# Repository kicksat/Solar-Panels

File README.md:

# solar-panels

Solar panels for the KickSat-2 CubeSat

# License

[Creative Commons Attribution-ShareAlike 4.0 International](https://creativecommons.org/licenses/by-sa/4.0/)

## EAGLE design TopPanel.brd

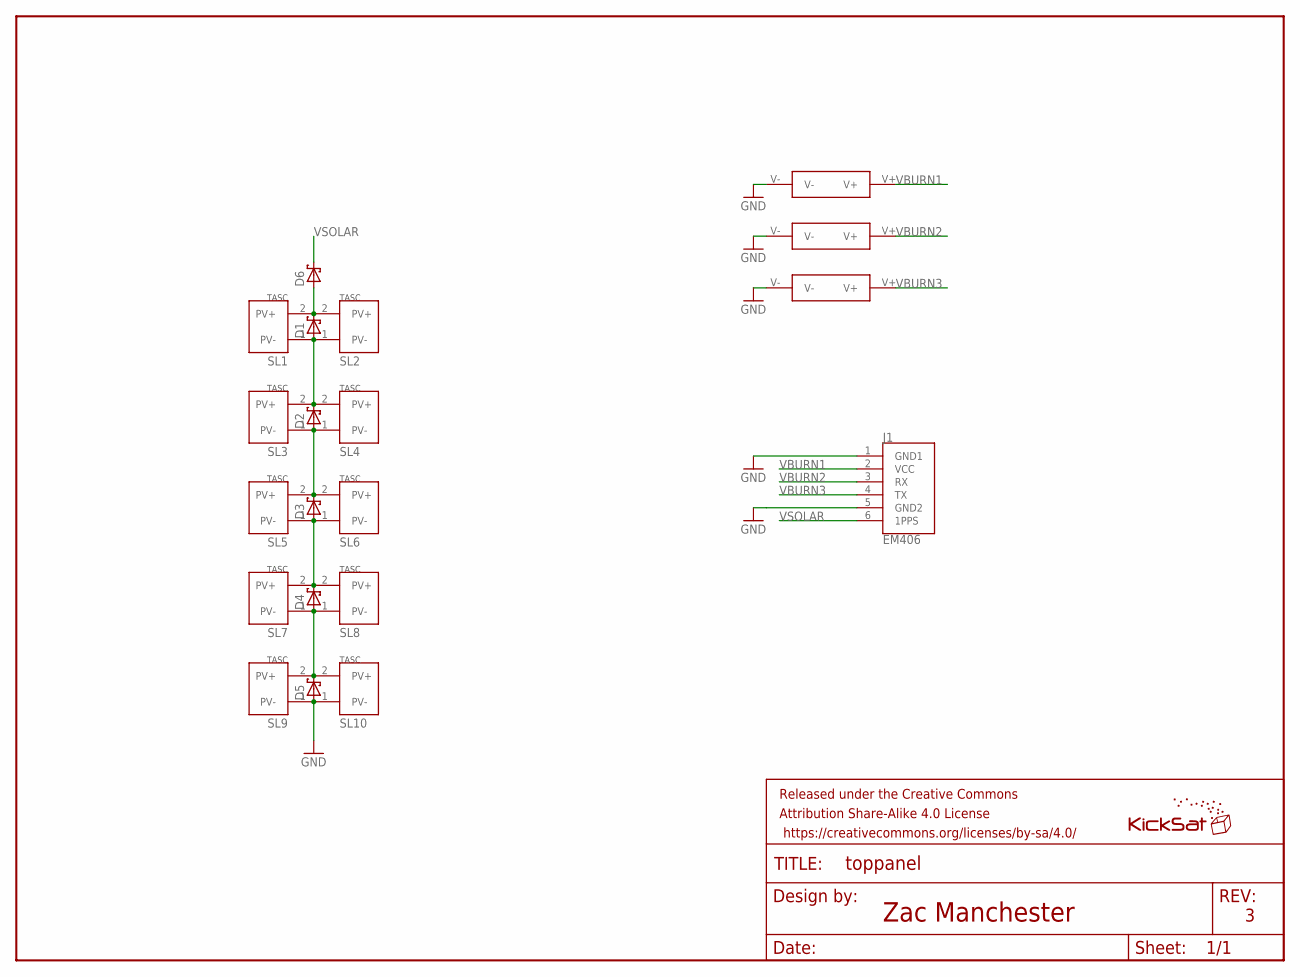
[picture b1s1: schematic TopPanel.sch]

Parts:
D1, D2, D3, D4, D5, D6: SB_DIODE
FRAME1: FRAME-LETTER; CREATIVE_COMMONS
J1: EM406; 1X06-1MM
SL1, SL2, SL3, SL4, SL5, SL6, SL7, SL8, SL9, SL10: SOLAR_CELL
U$1: KICKSAT_LOGO
U$2, U$3, U$4: BURNWIRE

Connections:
GND: D5.POS, J1.1 (GND1), J1.5 (GND2), SL9.1 (PV-), SL10.1 (PV-), U$2.V-, U$3.V-, U$4.V-
unnamed: D1.NEG, D6.POS, SL1.2 (PV+), SL2.2 (PV+)
unnamed: D2.POS, D3.NEG, SL3.1 (PV-), SL4.1 (PV-), SL5.2 (PV+), SL6.2 (PV+)
unnamed: D3.POS, D4.NEG, SL5.1 (PV-), SL6.1 (PV-), SL7.2 (PV+), SL8.2 (PV+)
unnamed: D1.POS, D2.NEG, SL1.1 (PV-), SL2.1 (PV-), SL3.2 (PV+), SL4.2 (PV+)
unnamed: D4.POS, D5.NEG, SL7.1 (PV-), SL8.1 (PV-), SL9.2 (PV+), SL10.2 (PV+)
VBURN1: J1.2 (VCC), U$2.V+
VBURN2: J1.3 (RX), U$3.V+
VBURN3: J1.4 (TX), U$4.V+
VSOLAR: D6.NEG, J1.6 (1PPS)

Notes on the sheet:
Zac Manchester

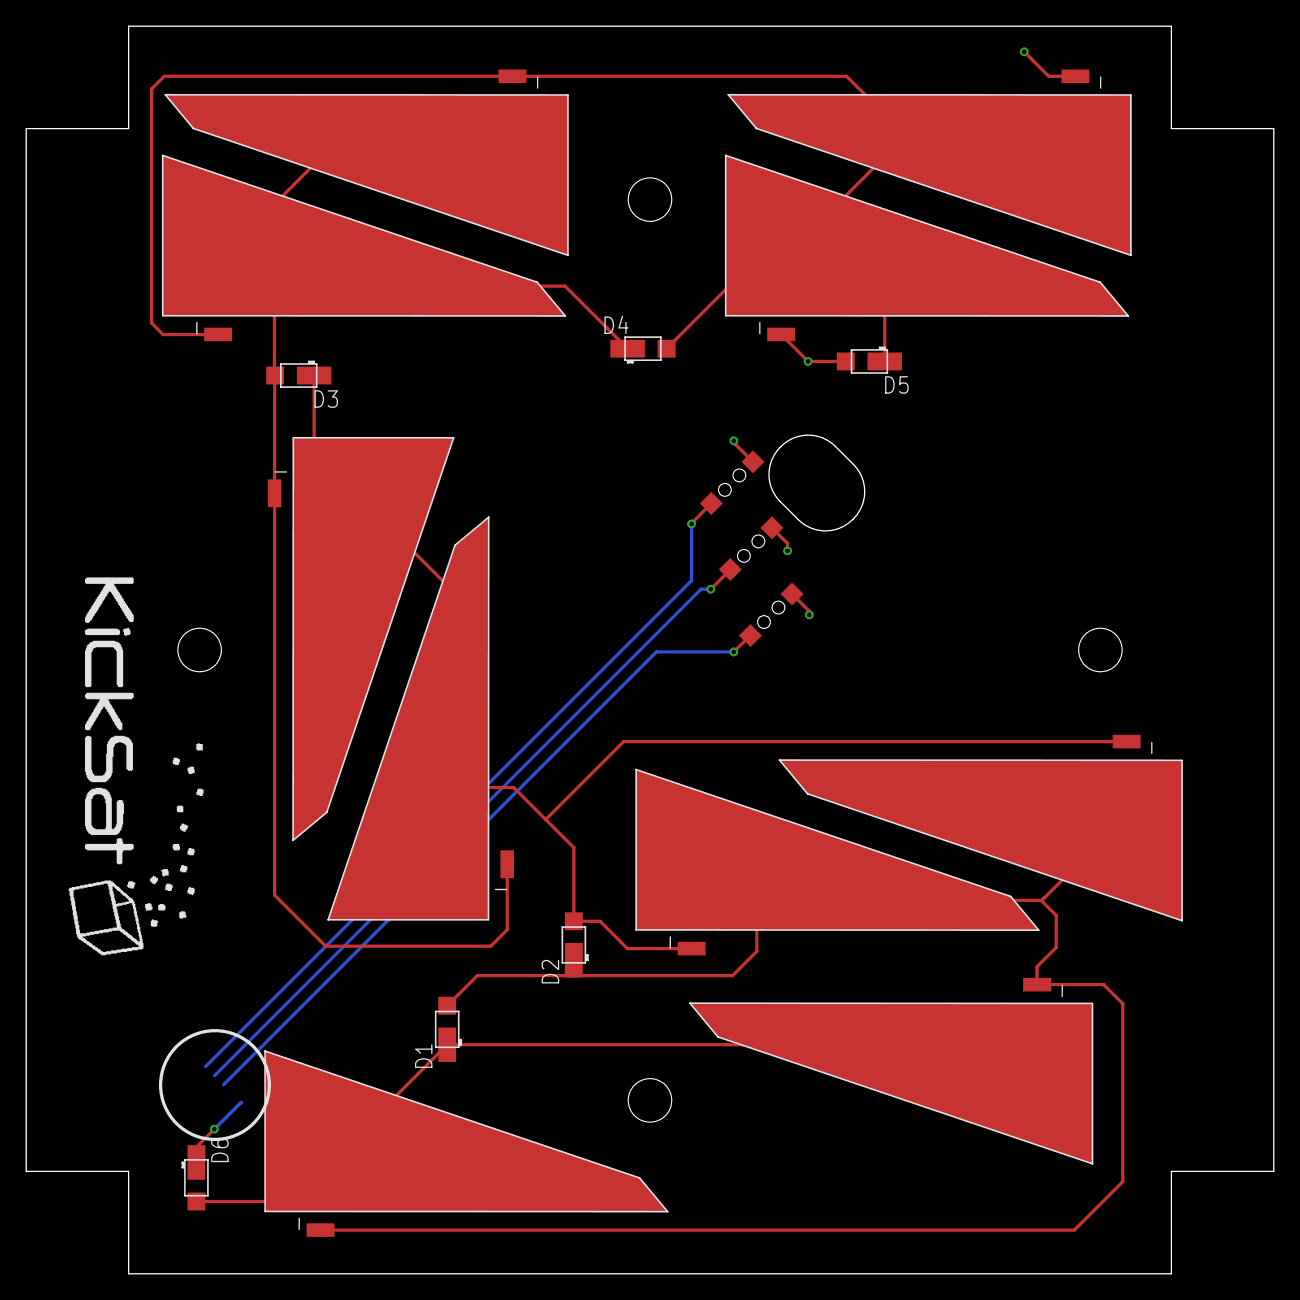
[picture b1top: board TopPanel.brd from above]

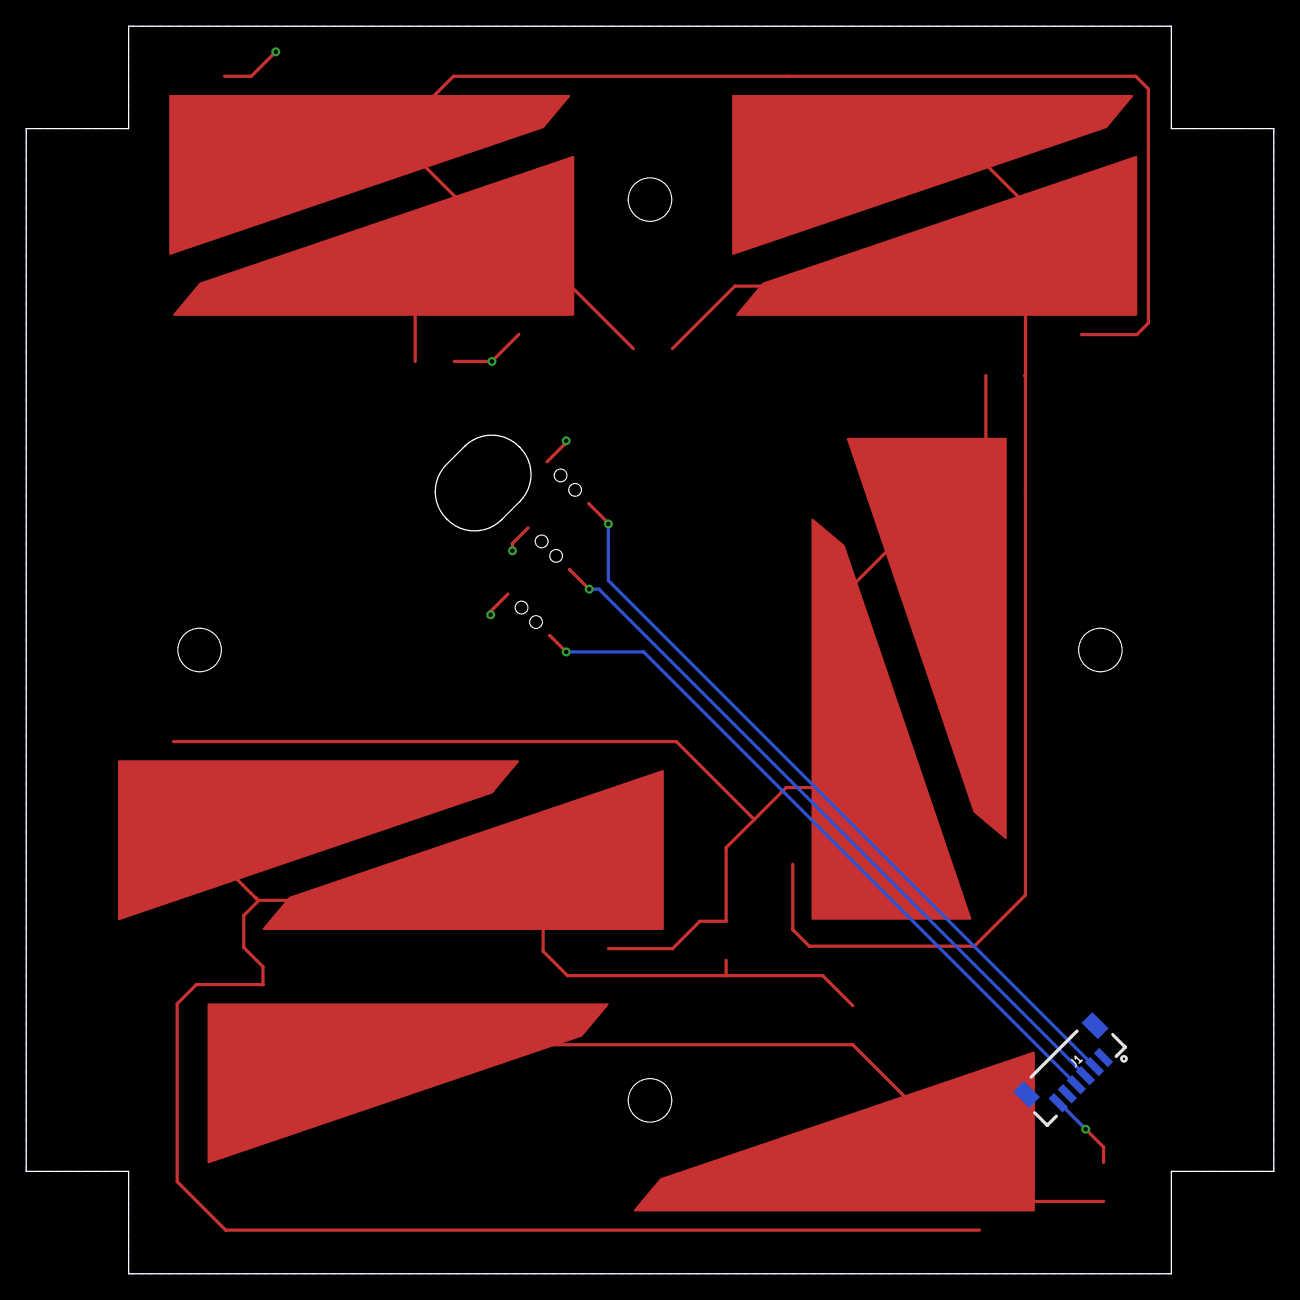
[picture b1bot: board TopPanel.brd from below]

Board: 2 copper layers, 97.5 x 97.5 mm, 22 parts (2 on the bottom side), 10 nets.

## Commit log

2018-04-11 Initial commit of KickSat-2 solar panels
2018-07-20 Set theme jekyll-theme-midnight
2018-08-27 New top panel outline
2018-08-27 Holes in the right spots...
2018-08-27 Connector swap
2018-08-28 put connector in correct spot
2018-08-28 Started routing
2018-08-29 Finished layout
2018-08-29 Adding Gerbers

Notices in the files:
parts and their libraries:
SparkFun-Aesthetics: Licensing: Creative Commons ShareAlike 4.0 International - https://creativecommons.org/licenses/by-sa/4.0
SparkFun-Aesthetics: Released under the Creative Commons Attribution Share-Alike 4.0 License
SparkFun-Aesthetics: Released under the Creative Commons
